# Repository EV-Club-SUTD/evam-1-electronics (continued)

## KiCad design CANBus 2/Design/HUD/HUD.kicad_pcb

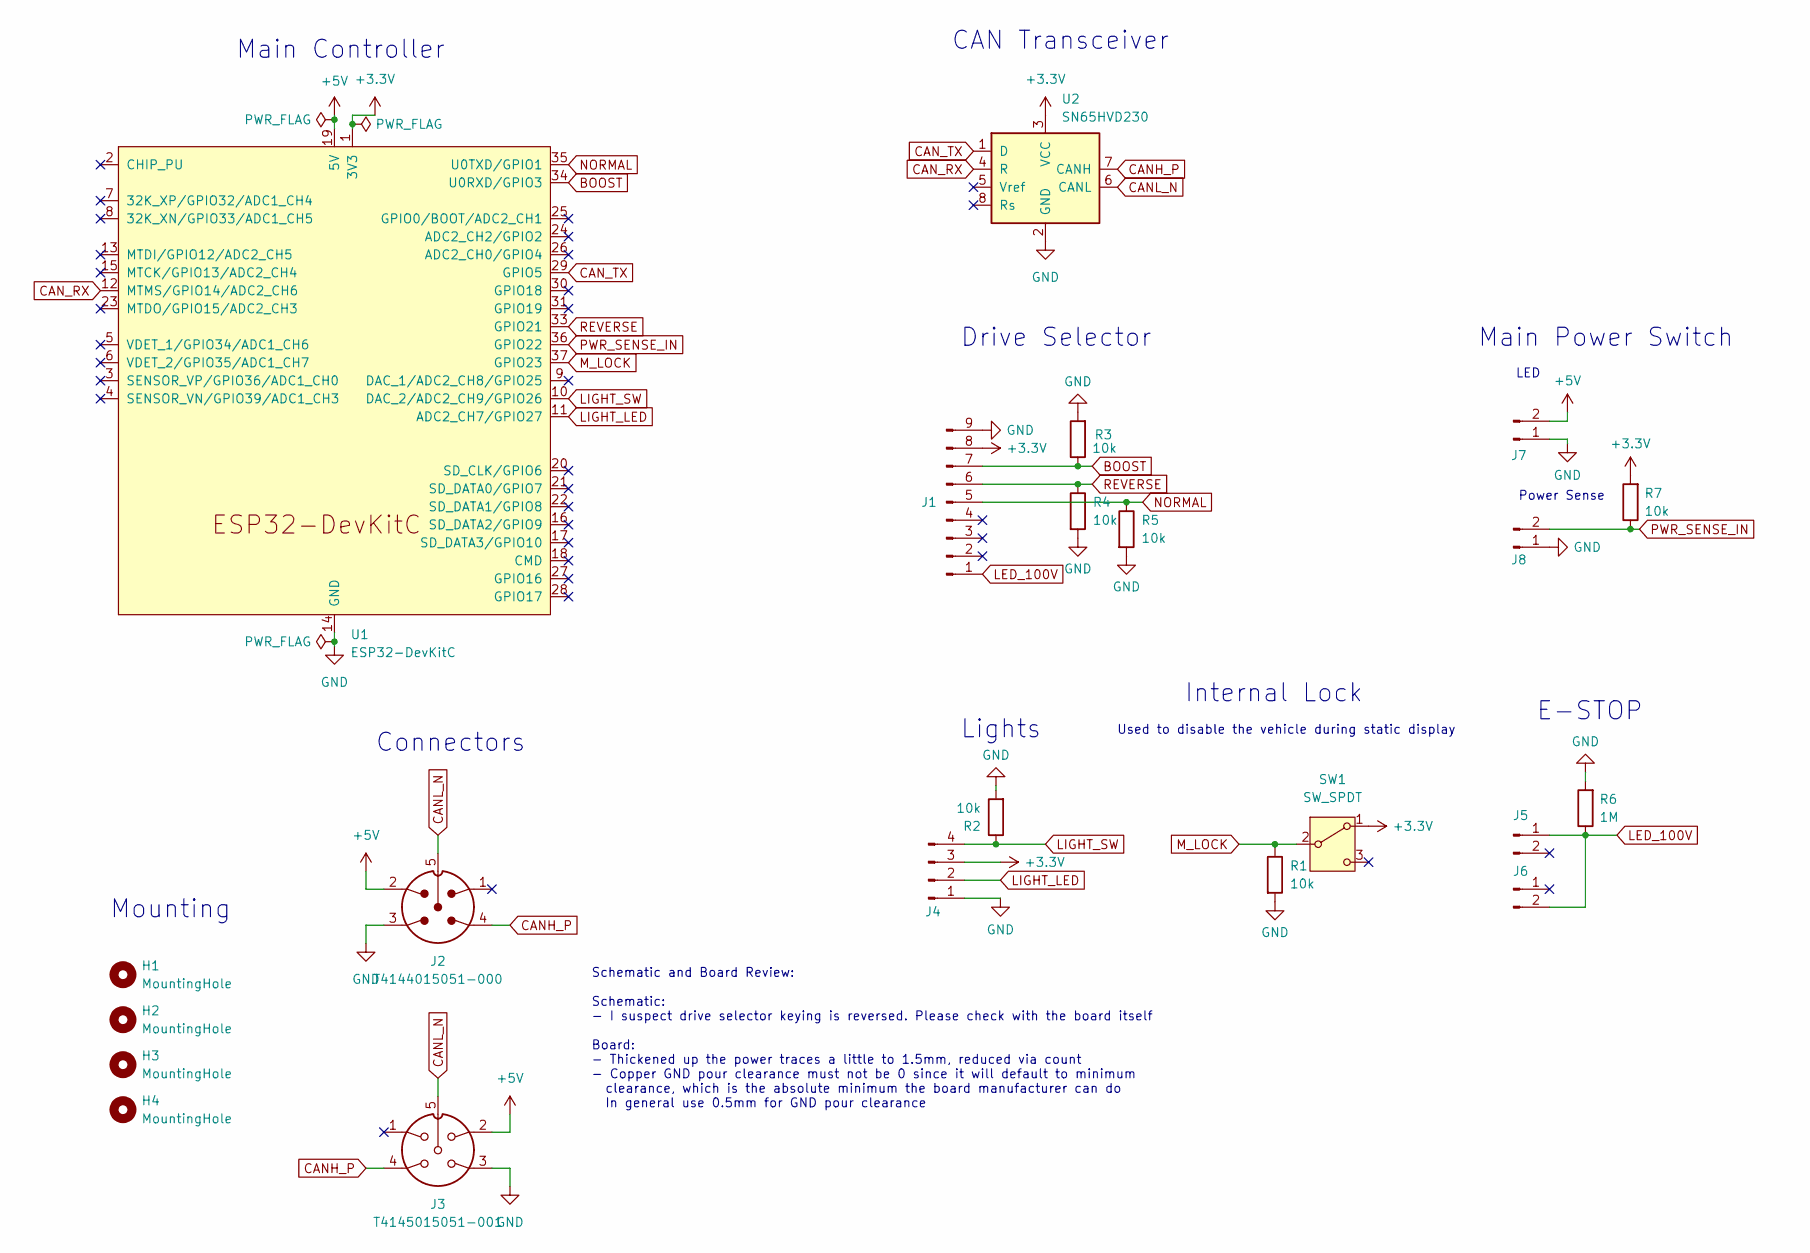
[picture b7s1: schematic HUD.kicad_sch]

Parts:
H1, H2, H3, H4: MountingHole; MountingHole_3.2mm_M3_ISO14580
J1: Conn_01x09_Pin; Molex_KK-254_AE-6410-09A_1x09_P2.54mm_Vertical
J2: T4144015051-000; M12-P5A-GPL; PARTREV A
J3: T4145015051-001; M12-S5A-GPL; PARTREV A
J4: Conn_01x04_Pin; Molex_KK-254_AE-6410-04A_1x04_P2.54mm_Vertical
J5, J6, J7, J8: Conn_01x02_Pin; Molex_KK-254_AE-6410-02A_1x02_P2.54mm_Vertical
R1, R2, R3, R4, R5, R7: 10k; R_0603_1608Metric
R6: 1M; R_1206_3216Metric
SW1: SW_SPDT; SW_SPDT_MT-0-103-F001-T000-RS
U1: ESP32-DevKitC
U2: SN65HVD230; SOIC-8_3.9x4.9mm_P1.27mm

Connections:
+3.3V: J1.8, J4.3, R7.2, SW1.1 (A), U1.1 (3V3), U2.3 (VCC)
+5V: J2.2, J3.2, J7.2, U1.19 (5V)
BOOST: J1.7, R3.1, U1.34 (U0RXD/GPIO3)
CANH_P: J2.4, J3.4, U2.7 (CANH)
CANL_N: J2.5, J3.5, U2.6 (CANL)
CAN_RX: U1.12 (MTMS/GPIO14/ADC2_CH6), U2.4 (R)
CAN_TX: U1.29 (GPIO5), U2.1 (D)
GND: J1.9, J2.3, J3.3, J4.1, J7.1, J8.1, R1.2, R2.2, R3.2, R4.2, R5.2, R6.2, U1.14 (GND), U1.32 (GND), U1.38 (GND), U2.2 (GND)
LED_100V: J1.1, J5.1, J6.2, R6.1
LIGHT_LED: J4.2, U1.11 (ADC2_CH7/GPIO27)
LIGHT_SW: J4.4, R2.1, U1.10 (DAC_2/ADC2_CH9/GPIO26)
M_LOCK: R1.1, SW1.2 (B), U1.37 (GPIO23)
NORMAL: J1.5, R5.1, U1.35 (U0TXD/GPIO1)
PWR_SENSE_IN: J8.2, R7.1, U1.36 (GPIO22)
REVERSE: J1.6, R4.1, U1.33 (GPIO21)

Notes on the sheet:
Used to disable the vehicle during static display
Lights
CAN Transceiver
Schematic and Board Review: Schematic: - I suspect drive selector keying is reversed. Please check with the board itself Board: - Thickened up the power traces a little to 1.5mm, reduced via count - Copper GND pour clearance must not be 0 since it will default to minimum clearance, which is the abs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
LED
Power Sense
Mounting
Main Controller
E-STOP
Main Power Switch
Connectors
Internal Lock
Drive Selector

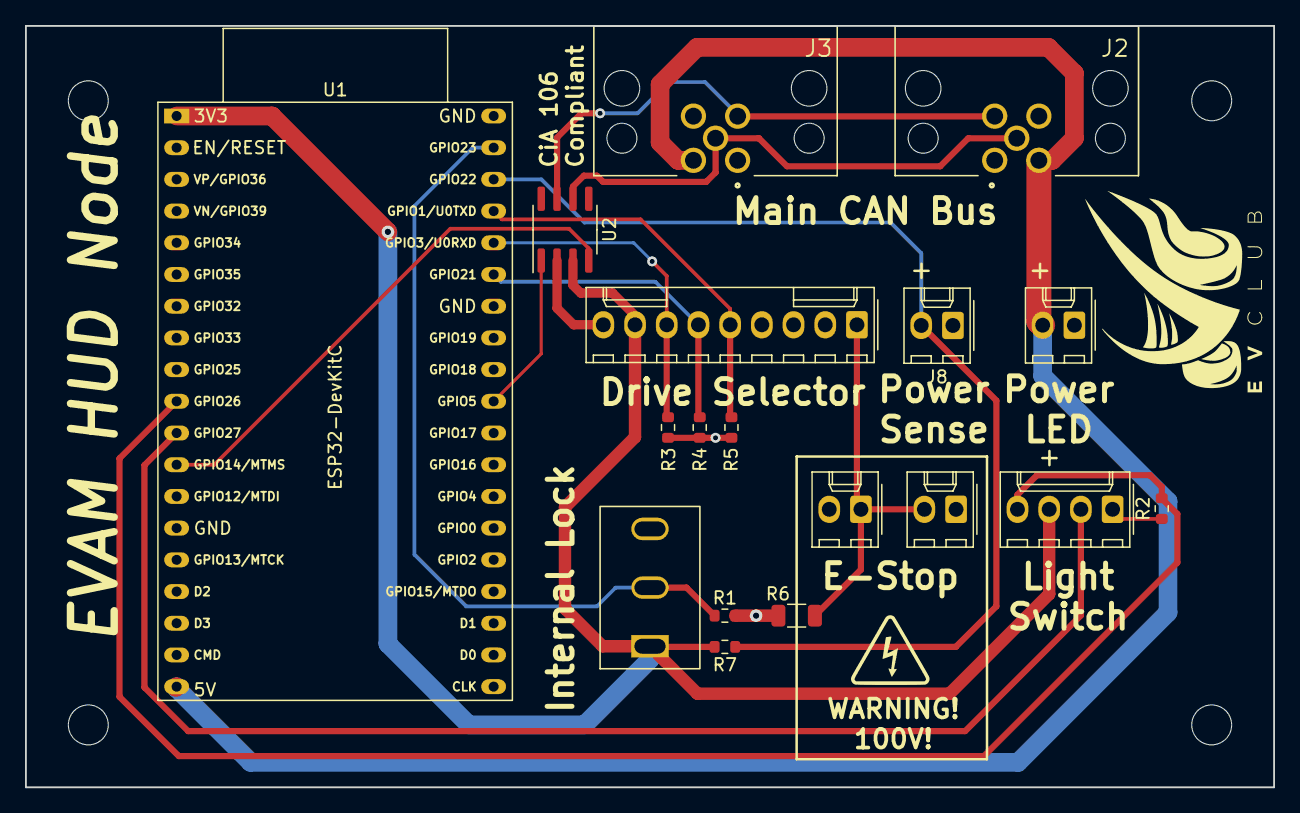
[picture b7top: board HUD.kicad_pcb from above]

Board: 2 copper layers, 100.0 x 61.0 mm, 22 parts (0 on the bottom side), 15 nets.

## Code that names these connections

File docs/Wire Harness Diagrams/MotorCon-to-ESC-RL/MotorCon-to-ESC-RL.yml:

metadata:
  title: MotorCon-to-ESC-RL
  authors:
    Created:
      name: EVAM
      date: 2025-08-06

connectors:
  C1:
    # General
    type: Aptiv SICMA
    subtype: Female
    image:
      src: img/Delphi-24-pinout.png
      width: 400
    notes: Device side diagram is shown

    # Purchase
    ignore_in_bom: false
    manufacturer: Aptiv (formerly Delphi)
    mpn: 211PC249S0031
    supplier: Mouser
    spn: 649-211PC249S0031

    # Pinout
    pincount: 24
    pins: [A1, A2, A3, A4, A5, A6, A7, A8, B1, B2, B3, B4, B5, B6, B7, B8, C1, C2, C3, C4, C5, C6, C7, C8]
    pinlabels: [RTN (High Voltage Power Negative), 12V+ (for relay), ACC+ (DC+ for Accelerator), STL (~Stop), BST (Boost), OUT (Logic out), 1HC (Hall sensor C), VH (DC+ for Hall sensor), Vkey (Power on), L- (relay signal), ACC-OUT (Accelerator), R (Reverse), IN1 (Eco), MS (Pulse output), 1HB (Hall sensor B), THM (Motor thermistor), NC, 12V-, STH (Stop), F (Forward), ALM (~Motor Lock), BEMF (Back EMF), 1HA (Hall sensor A), RTN (High Voltage Power GND)]

  C2:
    # General
    type: Furukawa RFW
    subtype: Female
    image:
      src: img/FW-C-6F-B-pinout.png
      width: 350
    notes: Cable side is shown

    # Purchase
    ignore_in_bom: false
    manufacturer: Furukawa
    mpn: FW-C-6F-B
    supplier: Aliexpress
    spn: DJ7061Y-2.3-11

    # Pinout
    pincount: 6
    pinlabels: [H1,H2,H3,H4,H5,H6]
  
  C3:
    # General
    type: Molex KK254
    subtype: Female
    image:
      src: img/MolexKK254-9-pinout.png
      width: 300
    notes: Cable side is shown

    # Purchase
    ignore_in_bom: false
    manufacturer: Molex
    mpn: 22013097
    supplier: DigiKey
    spn: WM2007-MD

    # Pinout
    pincount: 9
    pinlabels: [LOCK,NC,PULSE,REVERSE,ECO,BOOST,GND,ACC,EXTRA]
  
  # TODO: Check if C4 is defined correctly
  C4:
    # General
    type: JST RCY
    subtype: Plug
    image:
      src: img/JST-RCY-pinout-plug.png
      width: 400
    notes: Cable side is shown

    # Purchase
    ignore_in_bom: false
    manufacturer: JST
    mpn: SYR-02T
    supplier: DigiKey
    spn: 455-2653-ND

    # Pinout
    pincount: 2
    pinlabels: [J1, J2] # J1 is not implemented
  
  HS1: # this is a piece of heat shrink'd solder joint
    style: simple
    type: Heat shrink solder joint
    subtype: 22 AWG

cables:
  W1:
    category: bundle
    gauge: 22 AWG
    length: 0.5 m
    colors: [GNBK, BN, BU, RD, PK, YEBK, VT, GYBK, YEGN, GN, WH, YE, BK, BK] # Note that VT is actually sky blue
    notes: "NOTE: VT is actually sky blue"
  
  W2:
    gauge: 22 AWG
    length: 0.1 m
    colors: [RD]
    wirecount: 1

connections:
# If using Anaconda to manage Python environments, 
# please activate conda environment wireviz before compiling
  - # C1 to C2
    - C1: [A7, A8, B7, B8, C7, C8]
    - W1: [3, 4, 10, 11, 12, 13]
    - C2: [3, 4, 2, 5, 1, 6]
  
  - # C1 to C3
    - C1: [A4, A5, B3, B4, B5, B6, A1]
    - W1: [1, 2, 6, 7, 8, 9, 14]
    - C3: [1, 6, 4, 8, 5, 3, 7]

  - # C1 to C4
    - C1: [B1]
    - W1: [5]
    - HS1: [1]
    - W2: [1]
    - C4: [2]

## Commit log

2025-05-19 initial commit of all relevant assets to EVAM canbus 2
2025-05-22 added datasheets of the vehicle components
2025-06-26 added diagram templates
2025-08-01 changed folder organisation for datasheets
2025-08-08 added first wire harness diagram
2025-08-08 added new connection for wire diagram
2025-08-08 did wiring for all connections except JST RCY
2025-08-08 inserted placeholder for JST RCY connector
2025-08-08 defined JST RCY connector
2025-08-08 corrected model number for JST RCY
2025-08-09 added images for the motor wire harness
2025-08-12 completed motor RL diagram
2025-08-14 fixed furukawa and JST RCY pinouts
2025-08-22 new master cable diagram (incomplete!)
2025-09-08 preliminary edits to the master cable diagram
2025-09-08 added M12 connector diagram for CAN CiA106 standard
2025-09-08 updated M12 connector picture in diagram
2025-09-09 added E-stop connections to master cable
2025-09-09 more edits to master cable diagram(?), but estop switch currently displayed with placeholder W10. RCY female male stuff may be dodgy
2025-09-09 updated all JST RCY images
2025-09-16 fixed 3d models with new envvar
2025-09-25 overall system wiring png and draw.io file
2026-02-26 added new HUD dashboard files
